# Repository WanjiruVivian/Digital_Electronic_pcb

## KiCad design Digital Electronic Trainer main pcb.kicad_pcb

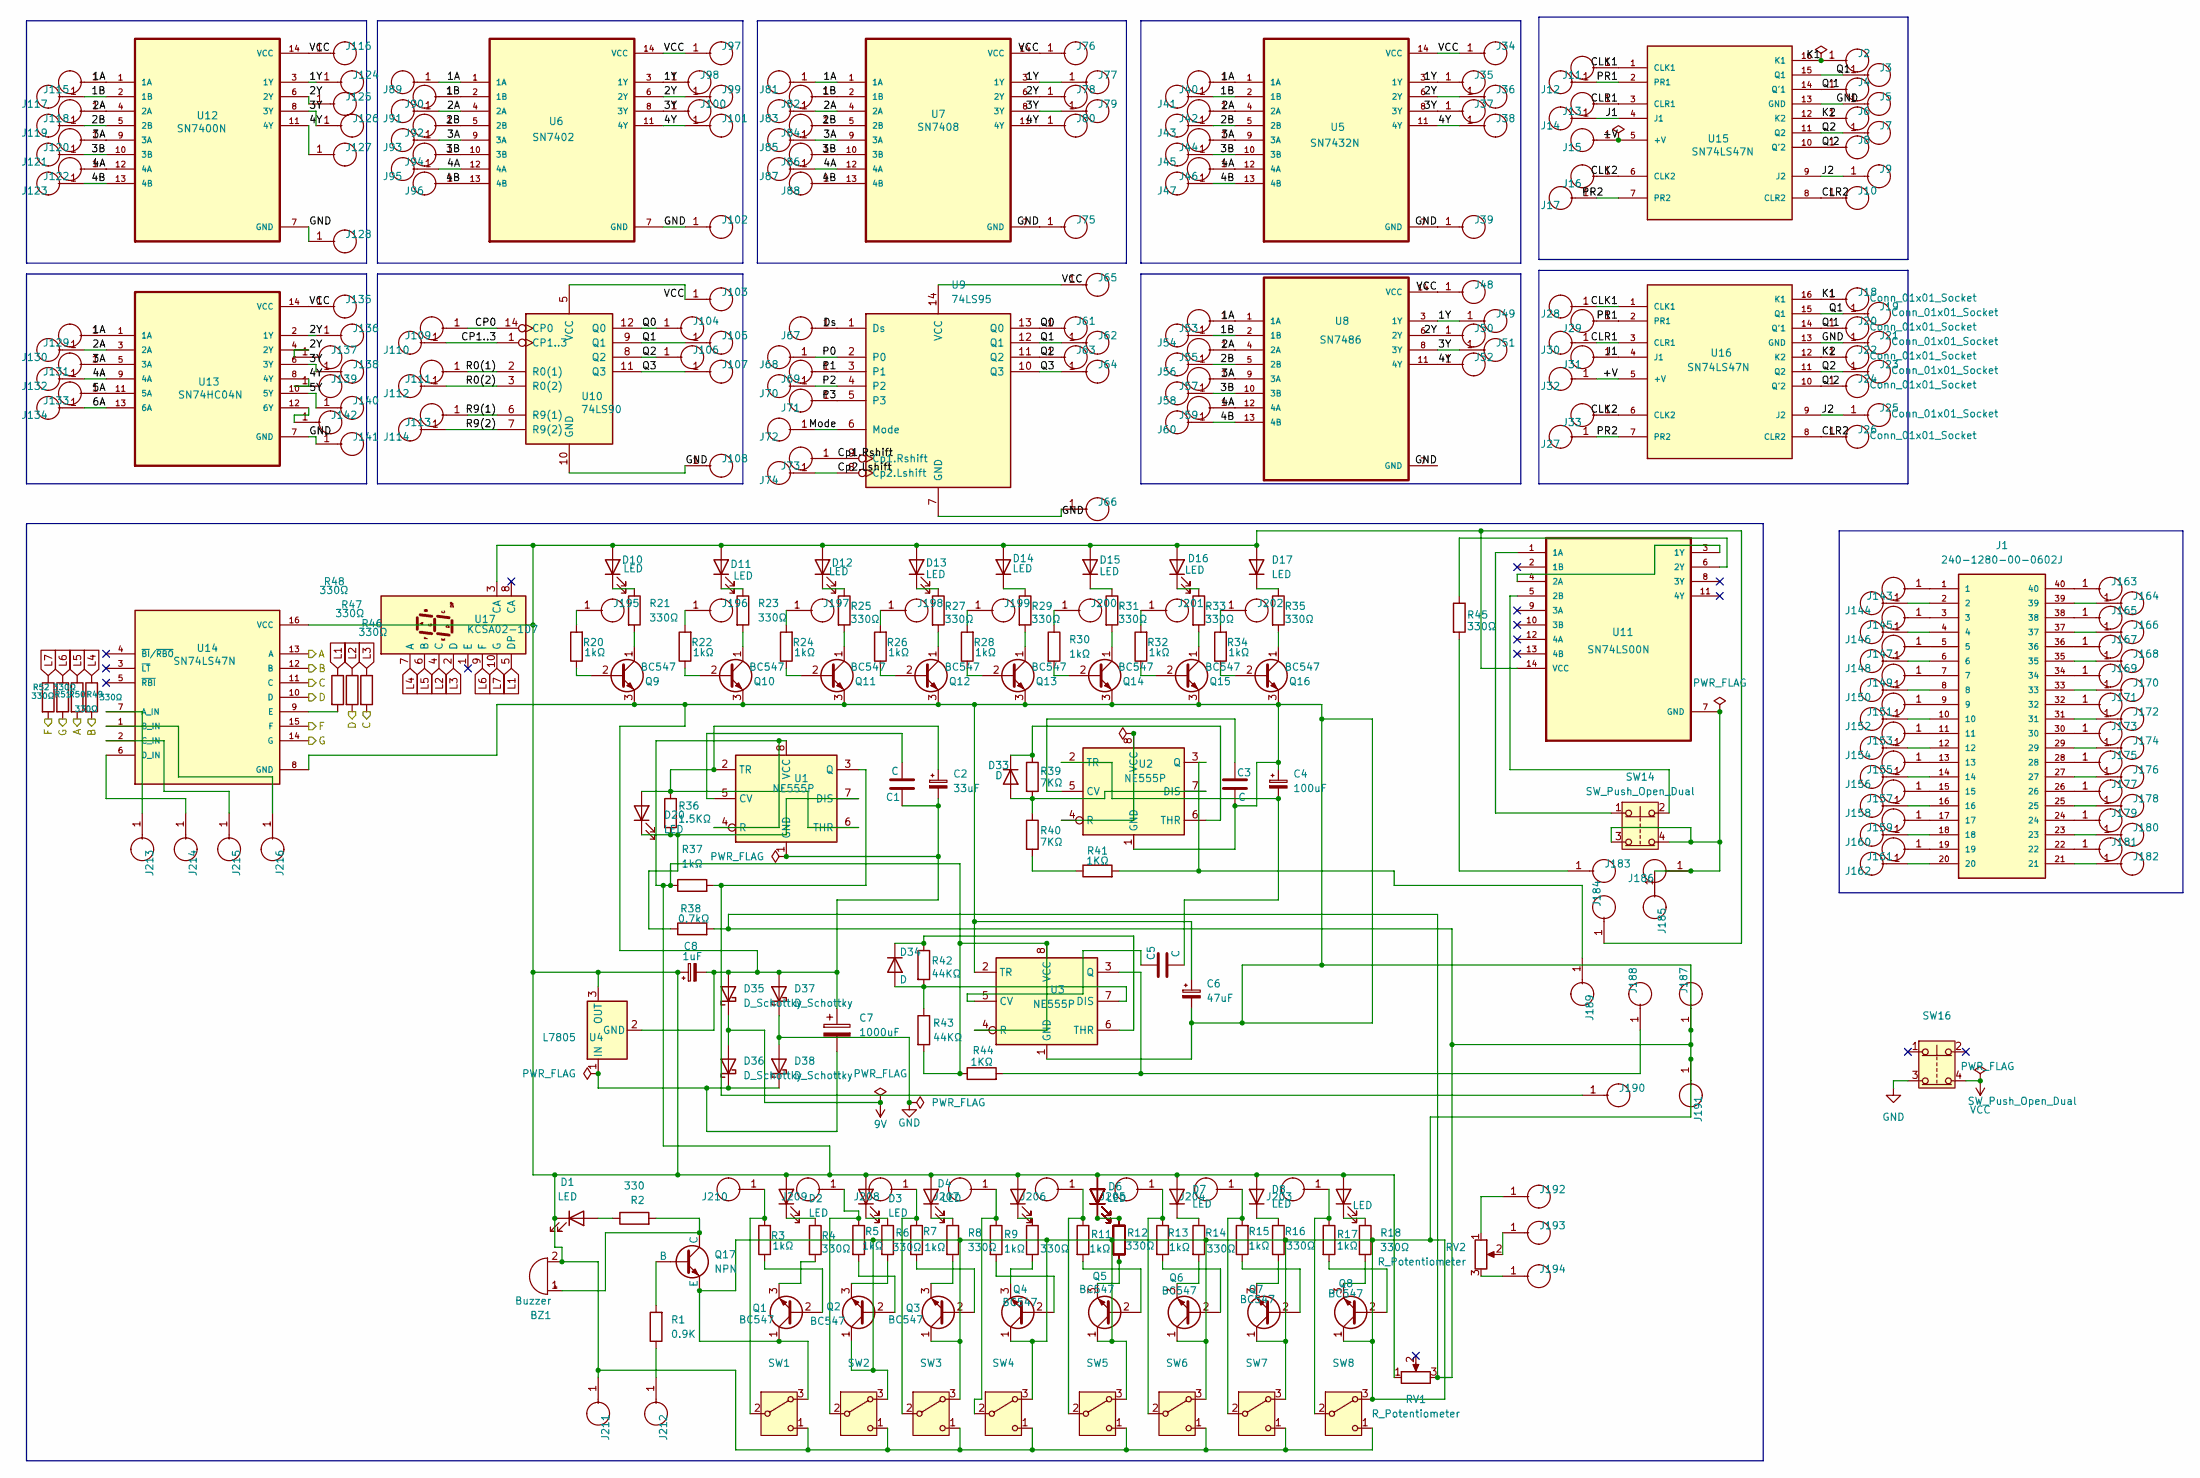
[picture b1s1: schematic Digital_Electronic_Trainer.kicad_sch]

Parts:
BZ1: Buzzer; Buzzer_D14mm_H7mm_P10mm
C1, C3, C5: C; C_Disc_D10.0mm_W2.5mm_P5.00mm
C2: 33uF; C_Radial_D10.0mm_H16.0mm_P5.00mm
C4: 100uF; C_Radial_D10.0mm_H16.0mm_P5.00mm
C6: 47uF; C_Radial_D10.0mm_H16.0mm_P5.00mm
C7: 1000uF; C_Radial_D12.5mm_H25.0mm_P5.00mm
C8: 1uF; C_Radial_D5.0mm_H11.0mm_P2.00mm
D1, D2, D3, D4, D5, D6, D7, D8, D9, D10, D11, D12, D13, D14, D15, D16, D17, D20, D24, D25, D26: LED; LED_D5.0mm
D33, D34: D; D_DO-34_SOD68_P12.70mm_Horizontal
D35, D36, D37, D38: D_Schottky; D_A-405_P12.70mm_Horizontal
J1: 240-1280-00-0602J; 3M_240-1280-00-0602J; PARTREV E
J2, J3, J4, J5, J6, J7, J8, J9, J10, J11, J12, J13, J14, J15, J16, J17, J18, J19, J20, J21, J22, J23, J24, J25, J26, J27, J28, J29, J30, J31, J32, J33, J34, J35, J36, J37, J38, J39, J40, J41, J42, J43, J44, J45, J46, J47, J48, J49, J50, J51, J52, J53, J54, J55, J56, J57, J58, J59, J60, J61, J62, J63, J64, J65, J66, J67, J68, J69, J70, J71, J72, J73, J74, J75, J76, J77, J78, J79, J80, J81, J82, J83, J84, J85, J86, J87, J88, J89, J90, J91, J92, J93, J94, J95, J96, J97, J98, J99, J100, J101, J102, J103, J104, J105, J106, J107, J108, J109, J110, J111, J112, J113, J114, J115, J116, J117, J118, J119, J120, J121, J122, J123, J124, J125, J126, J127, J128, J129, J130, J131, J132, J133, J134, J135, J136, J137, J138, J139, J140, J141, J142, J143, J144, J145, J146, J147, J148, J149, J150, J151, J152, J153, J154, J155, J156, J157, J158, J159, J160, J161, J162, J163, J164, J165, J166, J167, J168, J169, J170, J171, J172, J173, J174, J175, J176, J177, J178, J179, J180, J181, J182, J183, J184, J185, J186, J187, J188, J189, J190, J191, J192, J193, J194, J195, J196, J197, J198, J199, J200, J201, J202, J203, J204, J205, J206, J207, J208, J209, J210, J211, J212, J213, J214, J215, J216: Conn_01x01_Socket; PinSocket_1x01_P2.00mm_Vertical
Q1, Q2, Q3, Q4, Q5, Q6, Q7, Q8, Q9, Q10, Q11, Q12, Q13, Q14, Q15, Q16: BC547; TO-92_Inline
Q17: NPN; TO18
R1: 0.9K; R_Axial_DIN0309_L9.0mm_D3.2mm_P15.24mm_Horizontal
R2: 330; R_Axial_DIN0309_L9.0mm_D3.2mm_P15.24mm_Horizontal
R3, R5, R7, R9, R11, R13, R15, R17, R20, R22, R24, R26, R28, R30, R32, R34, R37: 1kΩ; R_Axial_DIN0309_L9.0mm_D3.2mm_P15.24mm_Horizontal
R4, R6, R8, R10, R12, R14, R16, R18, R21, R23, R25, R27, R29, R31, R33, R35: 330Ω; R_Axial_DIN0309_L9.0mm_D3.2mm_P15.24mm_Horizontal
R36: 1.5KΩ; R_Axial_DIN0309_L9.0mm_D3.2mm_P15.24mm_Horizontal
R38: 0.7kΩ; R_Axial_DIN0309_L9.0mm_D3.2mm_P15.24mm_Horizontal
R39, R40: 7KΩ; R_Axial_DIN0309_L9.0mm_D3.2mm_P15.24mm_Horizontal
R41, R44: 1KΩ; R_Axial_DIN0309_L9.0mm_D3.2mm_P15.24mm_Horizontal
R42, R43: 44KΩ; R_Axial_DIN0309_L9.0mm_D3.2mm_P15.24mm_Horizontal
R45, R46, R47, R48, R49, R50, R51, R52, R53, R55, R56: 330Ω; R_Axial_DIN0207_L6.3mm_D2.5mm_P15.24mm_Horizontal
RV1, RV2: R_Potentiometer; Potentiometer_Alps_RK09K_Single_Vertical
SW1, SW2, SW3, SW4, SW5, SW6, SW7, SW8: SW_Nidec_CAS-120A1; SW_ATE1D-2M3-10-Z
SW14: SW_Push_Open_Dual; SW_Push_2P1T_Toggle_CK_PVA1xxH2xxxxxxV2
SW16: SW_Push_Open_Dual; Push_E-Switch_KS01Q01
U1, U2, U3: NE555P; DIP-8_W7.62mm
U4: L7805; TO255P1040X460X1968-3
U5: SN7432N; DIP794W45P254L1969H508Q14
U6: SN7402; DIP794W45P254L1969H508Q14
U7: SN7408; DIP794W45P254L1969H508Q14
U8: SN7486; DIP794W45P254L1969H508Q14
U9: 74LS95; DIP794W45P254L1969H508Q16
U10: 74LS90; DIP254P762X508-14
U11: SN74LS00N; DIP794W45P254L1969H508Q14; DigiKey_Part_Number 296-1626-ND
U12: SN7400N; DIP794W45P254L1969H508Q14
U13: SN74HC04N; DIP794W45P254L1969H508Q14; DigiKey_Part_Number 2156-SN74HC04N-ND
U14: SN74LS47N; DIP794W45P254L1930H508Q16; PARTREV 12/2002; DigiKey_Part_Number 2156-SN74LS47N-ND
U15, U16: SN74LS47N; DIP794W45P254L1930H508Q16
U17: KCSA02-107; KCSC02-107

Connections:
9V: D35.1 (K), D36.2 (A)
/1A: J40.1, J53.1, J81.1, J89.1, J115.1, J129.1, U5.1 (1A), U6.1 (1A), U7.1 (1A), U8.1 (1A), U12.1 (1A), U13.1 (1A); also elsewhere on the board
/1B: J41.1, J54.1, J82.1, J90.1, J117.1, U5.2 (1B), U6.2 (1B), U7.2 (1B), U8.2 (1B), U12.2 (1B); also elsewhere on the board
/2A: J42.1, J55.1, J83.1, J91.1, J118.1, J130.1, U5.4 (2A), U6.4 (2A), U7.4 (2A), U8.4 (2A), U12.4 (2A), U13.3 (2A); also elsewhere on the board
/2B: J43.1, J56.1, J84.1, J92.1, J119.1, U5.5 (2B), U6.5 (2B), U7.5 (2B), U8.5 (2B), U12.5 (2B); also elsewhere on the board
/3A: J44.1, J57.1, J85.1, J93.1, J120.1, J131.1, U5.9 (3A), U6.9 (3A), U7.9 (3A), U8.9 (3A), U12.9 (3A), U13.5 (3A); also elsewhere on the board
/3B: J45.1, J58.1, J86.1, J94.1, J121.1, U5.10 (3B), U6.10 (3B), U7.10 (3B), U8.10 (3B), U12.10 (3B); also elsewhere on the board
/3Y: J37.1, J51.1, J79.1, J100.1, J126.1, J138.1, U5.8 (3Y), U6.8 (3Y), U7.8 (3Y), U8.8 (3Y), U12.8 (3Y), U13.6 (3Y); also elsewhere on the board
/4A: J46.1, J59.1, J87.1, J95.1, J122.1, J132.1, U5.12 (4A), U6.12 (4A), U7.12 (4A), U8.12 (4A), U12.12 (4A), U13.9 (4A); also elsewhere on the board
/4B: J47.1, J60.1, J88.1, J96.1, J123.1, U5.13 (4B), U6.13 (4B), U7.13 (4B), U8.13 (4B), U12.13 (4B); also elsewhere on the board
/4Y: J38.1, J52.1, J80.1, J101.1, J127.1, J139.1, U5.11 (4Y), U6.11 (4Y), U7.11 (4Y), U8.11 (4Y), U12.11 (4Y), U13.8 (4Y); also elsewhere on the board
/5A: J133.1, U13.11 (5A); also elsewhere on the board
/5Y: J140.1, U13.10 (5Y); also elsewhere on the board
/6A: J134.1, U13.13 (6A); also elsewhere on the board
/+V: J15.1, J32.1, U15.5 (+V), U16.5 (+V); also elsewhere on the board
/A: R50.2, U14.13 (A)
/B: R49.2, U14.12 (B)
/C: R46.2, U14.11 (C)
/CLK1: J11.1, J28.1, U15.1 (CLK1), U16.1 (CLK1); also elsewhere on the board
/CLK2: J16.1, J33.1, U15.6 (CLK2), U16.6 (CLK2); also elsewhere on the board
/CLR1: J13.1, J30.1, U15.3 (CLR1), U16.3 (CLR1); also elsewhere on the board
/CLR2: J10.1, J26.1, U15.8 (CLR2), U16.8 (CLR2); also elsewhere on the board
/CP0: J109.1, U10.14 (CP0); also elsewhere on the board
/CP1..3: J110.1, U10.1 (CP1..3); also elsewhere on the board
/Cp1.Rshift: J73.1, U9.9 (Cp1.Rshift); also elsewhere on the board
/Cp2.Lshift: J74.1, U9.8 (Cp2.Lshift); also elsewhere on the board
/D: R47.2, U14.10 (D)
/Ds: J67.1, U9.1 (Ds); also elsewhere on the board
/F: R52.2, U14.15 (F)
/G: R51.2, U14.14 (G)
/J1: J14.1, J31.1, U15.4 (J1), U16.4 (J1); also elsewhere on the board
/J2: J9.1, J25.1, U15.9 (J2), U16.9 (J2); also elsewhere on the board
/K1: J2.1, J18.1, U15.16 (K1), U16.16 (K1); also elsewhere on the board
/K2: J6.1, J22.1, U15.12 (K2), U16.12 (K2); also elsewhere on the board
/Mode: J72.1, U9.6 (Mode); also elsewhere on the board
/P0: J68.1, U9.2 (P0); also elsewhere on the board
/P1: J69.1, U9.3 (P1); also elsewhere on the board
/P2: J70.1, U9.4 (P2); also elsewhere on the board
/P3: J71.1, U9.5 (P3); also elsewhere on the board
/PR1: J12.1, J29.1, U15.2 (PR1), U16.2 (PR1); also elsewhere on the board
/PR2: J17.1, J27.1, U15.7 (PR2), U16.7 (PR2); also elsewhere on the board
/Q0: J61.1, J104.1, U9.13 (Q0), U10.12 (Q0); also elsewhere on the board
/Q2: J7.1, J23.1, J63.1, J106.1, U9.11 (Q2), U10.8 (Q2), U15.11 (Q2), U16.11 (Q2); also elsewhere on the board
/Q3: J64.1, J107.1, U9.10 (Q3), U10.11 (Q3); also elsewhere on the board
/Q'2: J8.1, J24.1, U15.10 (Q'2), U16.10 (Q'2); also elsewhere on the board
/R0(1): J111.1, U10.2 (R0(1)); also elsewhere on the board
/R0(2): J112.1, U10.3 (R0(2)); also elsewhere on the board
/R9(1): J113.1, U10.6 (R9(1)); also elsewhere on the board
/R9(2): J114.1, U10.7 (R9(2)); also elsewhere on the board
L1: R48.1, U17.5 (DP)
L2: R47.1, U17.4 (C)
L3: R46.1, U17.2 (D)
L4: R49.1, U17.7 (A)
L5: R50.1, U17.6 (B)
L6: R51.1, U17.9 (F)
L7: R52.1, U17.10 (G)
unnamed: BZ1.1 (+), Q17.1 (C), R2.2
unnamed: BZ1.2 (-), C8.1, D1.1 (K), D2.2 (A), D3.2 (A), D4.2 (A), D5.2 (A), D6.2 (A), D7.2 (A), D8.2 (A), D9.2 (A), D10.2 (A), D11.2 (A), D12.2 (A), D13.2 (A), D14.2 (A), D15.2 (A), D16.2 (A), D17.2 (A), D24.2 (A), D25.2 (A), D26.2 (A), J184.1, J211.1, R37.1, R43.2, R44.1, RV1.1, SW1.1 (C), SW2.1 (C), SW3.1 (C), SW4.1 (C), SW5.1 (C), SW6.1 (C), SW7.1 (C), SW8.1 (C), U1.4 (R), U1.8 (VCC), U3.4 (R), U3.8 (VCC), U4.3 (OUT), U11.14 (VCC), U14.16 (VCC), U17.3 (CA)
unnamed: D1.2 (A), R2.1
unnamed: D2.1 (K), R4.1
unnamed: D3.1 (K), R6.1
unnamed: D4.1 (K), R8.1
unnamed: D5.1 (K), R10.1
unnamed: D6.1 (K), D24.1 (K), D25.1 (K), D26.1 (K), R12.1, R53.1, R55.1, R56.1
unnamed: D7.1 (K), R14.1
unnamed: D8.1 (K), R16.1
unnamed: D9.1 (K), R18.1
unnamed: D10.1 (K), R21.1
unnamed: D11.1 (K), R23.1
unnamed: D12.1 (K), R25.1
unnamed: D13.1 (K), R27.1
unnamed: D14.1 (K), R29.1
unnamed: D15.1 (K), R31.1
unnamed: D16.1 (K), R33.1
unnamed: D17.1 (K), R35.1
unnamed: C2.1, D20.2 (A), R36.1, U1.2 (TR), U1.6 (THR)
unnamed: D20.1 (K), R36.2, R38.1, U1.7 (DIS)
unnamed: D33.2 (A), R39.2, R40.1, U2.7 (DIS)
unnamed: D33.1 (K), R39.1, U2.6 (THR)
unnamed: D34.2 (A), R42.2, R43.1, U3.7 (DIS)
unnamed: D34.1 (K), R42.1, U3.6 (THR)
unnamed: C1.1, C2.2, C3.2, C4.1, C6.1, C6.2, C7.1, C8.2, D35.2 (A), D37.2 (A), J187.1, J191.1, Q1.1 (C), Q2.1 (C), Q3.1 (C), Q4.1 (C), Q5.1 (C), Q6.1 (C), Q7.1 (C), Q8.1 (C), Q9.3 (E), Q10.3 (E), Q11.3 (E), Q12.3 (E), Q13.3 (E), Q14.3 (E), Q15.3 (E), Q16.3 (E), Q17.3 (E), R38.2, RV1.3, SW1.3 (A), SW2.3 (A), SW3.3 (A), SW4.3 (A), SW5.3 (A), SW6.3 (A), SW7.3 (A), SW8.3 (A), U1.1 (GND), U2.1 (GND), U3.1 (GND), U3.2 (TR), U4.2 (GND), U14.8 (GND)
unnamed: C7.2, D36.1 (K), D38.1 (K), U4.1 (IN)
unnamed 83: J142.1, U13.12 (6Y); also elsewhere on the board
unnamed: J1.1, J143.1
unnamed: J1.2, J144.1
unnamed: J1.3, J145.1
unnamed: J1.4, J146.1
unnamed: J1.5, J147.1
unnamed: J1.6, J148.1
unnamed: J1.7, J149.1
unnamed: J1.8, J150.1
unnamed: J1.9, J151.1
unnamed: J1.10, J152.1
unnamed: J1.11, J153.1
unnamed: J1.12, J154.1
unnamed: J1.13, J155.1
unnamed: J1.14, J156.1
unnamed: J1.15, J157.1
unnamed: J1.16, J158.1
unnamed: J1.17, J159.1
unnamed: J1.18, J160.1
unnamed: J1.19, J161.1
unnamed: J1.20, J162.1
unnamed: J1.40, J163.1
unnamed: J1.39, J164.1
unnamed: J1.38, J165.1
unnamed: J1.37, J166.1
unnamed: J1.36, J167.1
unnamed: J1.35, J168.1
unnamed: J1.34, J169.1
unnamed: J1.33, J170.1
unnamed: J1.32, J171.1
unnamed: J1.31, J172.1
unnamed: J1.30, J173.1
unnamed: J1.29, J174.1
unnamed: J1.28, J175.1
unnamed: J1.27, J176.1
unnamed: J1.26, J177.1
unnamed: J1.25, J178.1
unnamed: J1.24, J179.1
unnamed: J1.23, J180.1
unnamed: J1.22, J181.1
unnamed: J1.21, J182.1
unnamed: J183.1, R45.2
unnamed: J185.1, J186.1, SW14.3, SW14.4, U11.7 (GND)
unnamed: J188.1, R44.2, U3.3 (Q)
unnamed: J189.1, R41.2, U2.3 (Q)
unnamed: J190.1, R37.2, U1.3 (Q)
unnamed: J192.1, RV2.1
unnamed: J193.1, RV2.2
unnamed: J194.1, RV2.3
unnamed: J195.1, R20.2
unnamed: J196.1, R22.2
unnamed: J197.1, R24.2
unnamed: J198.1, R26.2
unnamed: J199.1, R28.2
unnamed: J200.1, R30.1
unnamed: J201.1, R32.2
unnamed: J202.1, R34.2
unnamed: J203.1, R17.1, SW8.2 (B)
unnamed: J204.1, R15.2, SW7.2 (B)
unnamed: J205.1, R13.1, SW6.2 (B)
unnamed: J206.1, R11.1, SW5.2 (B)
unnamed: J207.1, R9.1, SW4.2 (B)
unnamed: J208.1, R7.1, SW3.2 (B)
unnamed: J209.1, R5.1, SW2.2 (B)
unnamed: J210.1, R3.2, SW1.2 (B)
unnamed: J212.1, R1.1
unnamed: J213.1, U14.7 (A_IN)
unnamed: J214.1, U14.6 (D_IN)
unnamed: J215.1, U14.2 (C_IN)
unnamed: J216.1, U14.1 (B_IN)
unnamed: Q1.2 (B), R3.1
unnamed: Q1.3 (E), R4.2
unnamed: Q2.2 (B), R5.2
unnamed: Q2.3 (E), R6.2
unnamed: Q3.2 (B), R7.2
unnamed: Q3.3 (E), R8.2
unnamed: Q4.2 (B), R9.2
unnamed: Q4.3 (E), R10.2
unnamed: Q5.2 (B), R11.2
unnamed: Q5.3 (E), R12.2, R53.2, R55.2, R56.2
unnamed: Q6.2 (B), R13.2
unnamed: Q6.3 (E), R14.2
unnamed: Q7.2 (B), R15.1
unnamed: Q7.3 (E), R16.2
unnamed: Q8.2 (B), R17.2
unnamed: Q8.3 (E), R18.2
unnamed: Q9.2 (B), R20.1
unnamed: Q9.1 (C), R21.2
unnamed: Q10.2 (B), R22.1
unnamed: Q10.1 (C), R23.2
unnamed: Q11.2 (B), R24.1
unnamed: Q11.1 (C), R25.2
unnamed: Q12.2 (B), R26.1
unnamed: Q12.1 (C), R27.2
unnamed: Q13.2 (B), R28.1
unnamed: Q13.1 (C), R29.2
unnamed: Q14.2 (B), R30.2
unnamed: Q14.1 (C), R31.2
unnamed: Q15.2 (B), R32.1
unnamed: Q15.1 (C), R33.2
unnamed: Q16.2 (B), R34.1
unnamed: Q16.1 (C), R35.2
unnamed: Q17.2 (B), R1.2
unnamed: R40.2, R41.1
unnamed: C1.2, U1.5 (CV)
unnamed: C3.1, U2.5 (CV)
unnamed: U2.4 (R), U2.8 (VCC)
unnamed: C4.2, C5.2, U2.2 (TR)
unnamed: C5.1, U3.5 (CV)
unnamed: SW14.1, U11.1 (1A)
unnamed: U11.3 (1Y), U11.4 (2A)
unnamed: SW14.2, U11.5 (2B)
unnamed: R45.1, U11.6 (2Y)
unnamed: R48.2, U14.9 (E)
VCC: J34.1, J48.1, J65.1, J76.1, J97.1, J103.1, J116.1, J135.1, SW16.4, U5.14 (VCC), U6.14 (VCC), U7.14 (VCC), U8.14 (VCC), U9.14 (VCC), U10.5 (VCC), U12.14 (VCC), U13.14 (VCC); also elsewhere on the board

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
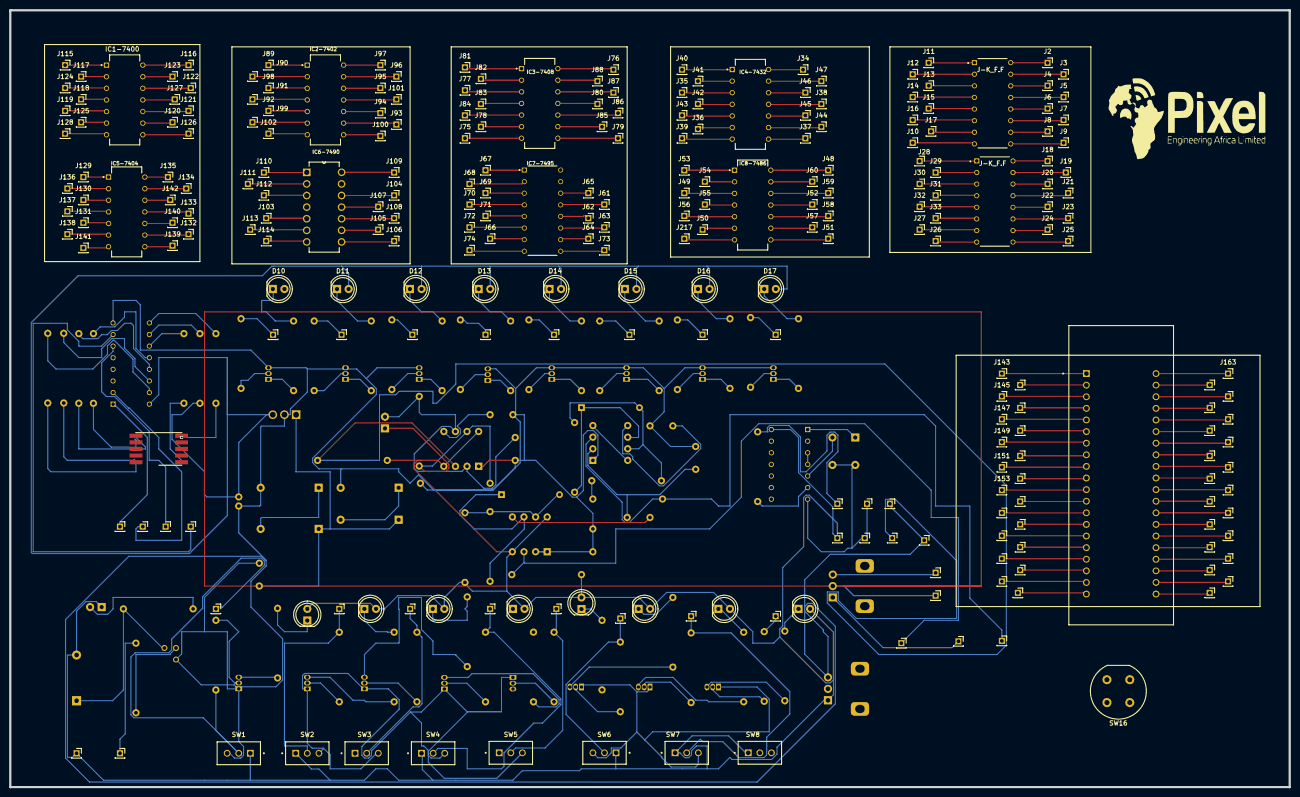
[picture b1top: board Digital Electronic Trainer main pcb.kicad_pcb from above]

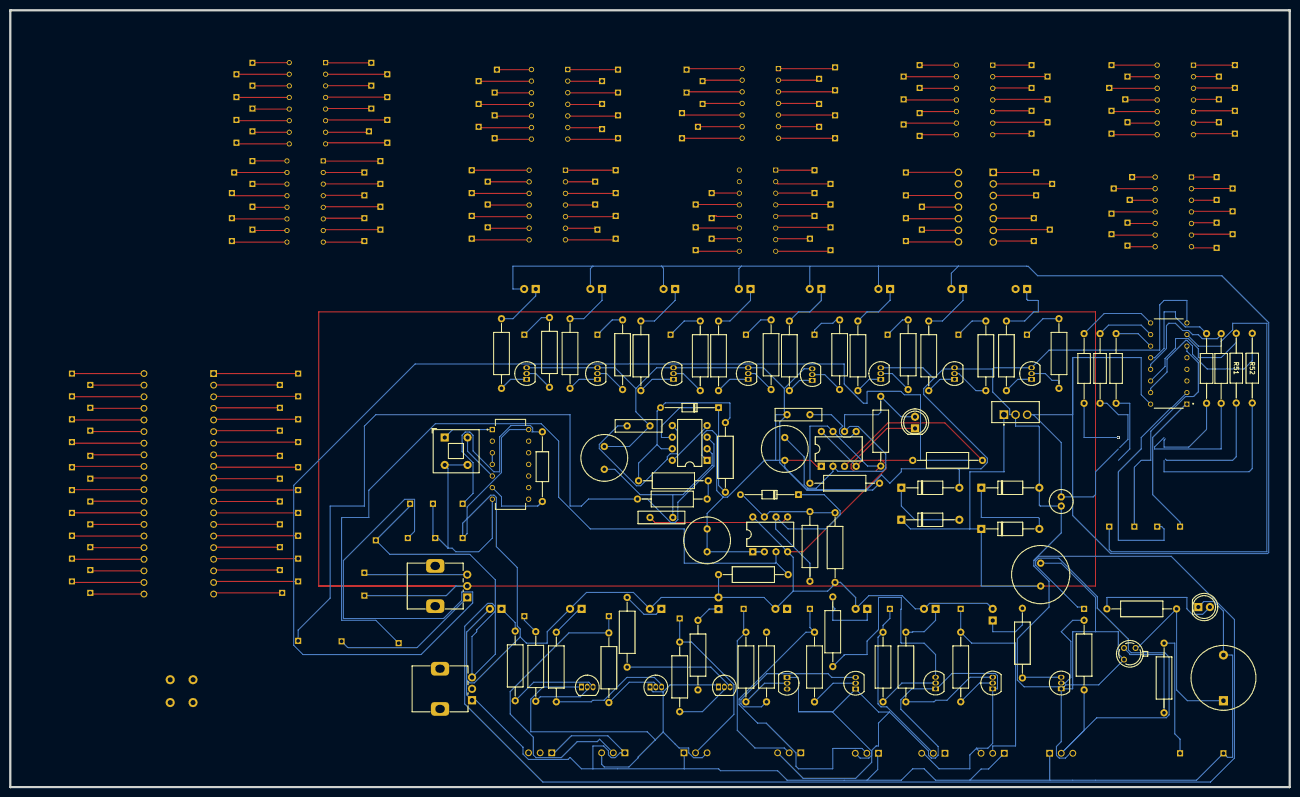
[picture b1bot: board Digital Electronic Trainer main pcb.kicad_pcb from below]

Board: 2 copper layers, 280.0 x 170.0 mm, 347 parts (94 on the bottom side), 208 nets.

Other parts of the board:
IC1-7400: SN7400N; DIP794W45P254L1969H508Q14
IC2-7402: SN7402; DIP794W45P254L1969H508Q14
IC3-7408: SN7408; DIP794W45P254L1969H508Q14
IC4-7432: SN7432N; DIP794W45P254L1969H508Q14
IC5-7404: SN74HC04N; DIP794W45P254L1969H508Q14
IC6-7490: 74LS90; DIP254P762X508-14
IC7-7495: 74LS95; DIP794W45P254L1969H508Q16
IC8-7486: SN7486; DIP794W45P254L1969H508Q14
J217: Conn_01x01_Socket; PinSocket_1x01_P2.00mm_Vertical
J-K_F.F, J-K_F.F#2: J-K F.F; DIP794W45P254L1930H508Q16

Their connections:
/1A: IC1-7400.1 (1A), IC2-7402.1 (1A), IC3-7408.1 (1A), IC4-7432.1 (1A), IC5-7404.1 (1A), IC8-7486.1 (1A); also elsewhere on the board
/1B: IC1-7400.2 (1B), IC2-7402.2 (1B), IC3-7408.2 (1B), IC4-7432.2 (1B), IC8-7486.2 (1B); also elsewhere on the board
/2A: IC1-7400.4 (2A), IC2-7402.4 (2A), IC3-7408.4 (2A), IC4-7432.4 (2A), IC5-7404.3 (2A), IC8-7486.4 (2A); also elsewhere on the board
/2B: IC1-7400.5 (2B), IC2-7402.5 (2B), IC3-7408.5 (2B), IC4-7432.5 (2B), IC8-7486.5 (2B); also elsewhere on the board
/3A: IC1-7400.9 (3A), IC2-7402.9 (3A), IC3-7408.9 (3A), IC4-7432.9 (3A), IC5-7404.5 (3A), IC8-7486.9 (3A); also elsewhere on the board
/3B: IC1-7400.10 (3B), IC2-7402.10 (3B), IC3-7408.10 (3B), IC4-7432.10 (3B), IC8-7486.10 (3B); also elsewhere on the board
/3Y: IC1-7400.8 (3Y), IC2-7402.8 (3Y), IC3-7408.8 (3Y), IC4-7432.8 (3Y), IC5-7404.6 (3Y), IC8-7486.8 (3Y); also elsewhere on the board
/4A: IC1-7400.12 (4A), IC2-7402.12 (4A), IC3-7408.12 (4A), IC4-7432.12 (4A), IC5-7404.9 (4A), IC8-7486.12 (4A); also elsewhere on the board
/4B: IC1-7400.13 (4B), IC2-7402.13 (4B), IC3-7408.13 (4B), IC4-7432.13 (4B), IC8-7486.13 (4B); also elsewhere on the board
/4Y: IC1-7400.11 (4Y), IC2-7402.11 (4Y), IC3-7408.11 (4Y), IC4-7432.11 (4Y), IC5-7404.8 (4Y), IC8-7486.11 (4Y); also elsewhere on the board
/5A: IC5-7404.11 (5A); also elsewhere on the board
/5Y: IC5-7404.10 (5Y); also elsewhere on the board
/6A: IC5-7404.13 (6A); also elsewhere on the board
/+V: J-K_F.F.5 (+V), J-K_F.F#2.5 (+V); also elsewhere on the board
/CLK1: J-K_F.F.1 (CLK1), J-K_F.F#2.1 (CLK1); also elsewhere on the board
/CLK2: J-K_F.F.6 (CLK2), J-K_F.F#2.6 (CLK2); also elsewhere on the board
/CLR1: J-K_F.F.3 (CLR1), J-K_F.F#2.3 (CLR1); also elsewhere on the board
/CLR2: J-K_F.F.8 (CLR2), J-K_F.F#2.8 (CLR2); also elsewhere on the board
/CP0: IC6-7490.14 (CP0); also elsewhere on the board
/CP1..3: IC6-7490.1 (CP1..3); also elsewhere on the board
/Cp1.Rshift: IC7-7495.9 (Cp1.Rshift); also elsewhere on the board
/Cp2.Lshift: IC7-7495.8 (Cp2.Lshift); also elsewhere on the board
/Ds: IC7-7495.1 (Ds); also elsewhere on the board
/J1: J-K_F.F.4 (J1), J-K_F.F#2.4 (J1); also elsewhere on the board
/J2: J-K_F.F.9 (J2), J-K_F.F#2.9 (J2); also elsewhere on the board
/K1: J-K_F.F.16 (K1), J-K_F.F#2.16 (K1); also elsewhere on the board
/K2: J-K_F.F.12 (K2), J-K_F.F#2.12 (K2); also elsewhere on the board
/Mode: IC7-7495.6 (Mode); also elsewhere on the board
/P0: IC7-7495.2 (P0); also elsewhere on the board
/P1: IC7-7495.3 (P1); also elsewhere on the board
/P2: IC7-7495.4 (P2); also elsewhere on the board
/P3: IC7-7495.5 (P3); also elsewhere on the board
/PR1: J-K_F.F.2 (PR1), J-K_F.F#2.2 (PR1); also elsewhere on the board
/PR2: J-K_F.F.7 (PR2), J-K_F.F#2.7 (PR2); also elsewhere on the board
/Q0: IC6-7490.12 (Q0), IC7-7495.13 (Q0); also elsewhere on the board
/Q2: IC6-7490.8 (Q2), IC7-7495.11 (Q2), J-K_F.F.11 (Q2), J-K_F.F#2.11 (Q2); also elsewhere on the board
/Q3: IC6-7490.11 (Q3), IC7-7495.10 (Q3); also elsewhere on the board
/Q'2: J-K_F.F.10 (Q'2), J-K_F.F#2.10 (Q'2); also elsewhere on the board
/R0(1): IC6-7490.2 (R0(1)); also elsewhere on the board
/R0(2): IC6-7490.3 (R0(2)); also elsewhere on the board
/R9(1): IC6-7490.6 (R9(1)); also elsewhere on the board
/R9(2): IC6-7490.7 (R9(2)); also elsewhere on the board
unnamed 83: IC5-7404.12 (6Y); also elsewhere on the board
VCC: IC1-7400.14 (VCC), IC2-7402.14 (VCC), IC3-7408.14 (VCC), IC4-7432.14 (VCC), IC5-7404.14 (VCC), IC6-7490.5 (VCC), IC7-7495.14 (VCC), IC8-7486.14 (VCC); also elsewhere on the board

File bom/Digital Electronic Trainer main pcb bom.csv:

"Id";"Designator";"Footprint";"Quantity";"Designation";"Supplier and ref";
1;"J215,J118,J166,J183,J128,J165,J150,J203,J74,J76,J86,J151,J106,J137,J188,J139,J104,J194,J157,J68,J120,J41,J117,J178,J52,J58,J177,J211,J24,J16,J17,J197,J204,J134,J143,J217,J34,J56,J29,J23,J132,J172,J107,J96,J189,J8,J196,J57,J40,J36,J99,J205,J59,J3,J101,J142,J193,J67,J131,J18,J123,J7,J167,J64,J9,J116,J108,J61,J213,J39,J154,J115,J77,J124,J174,J91,J158,J54,J27,J22,J2,J21,J62,J92,J186,J19,J168,J156,J28,J133,J160,J45,J161,J114,J11,J69,J185,J50,J195,J182,J112,J25,J119,J60,J75,J109,J149,J83,J181,J73,J163,J93,J184,J48,J111,J136,J88,J147,J46,J199,J145,J15,J200,J79,J210,J144,J95,J155,J47,J176,J20,J125,J190,J5,J141,J130,J89,J87,J207,J100,J121,J201,J206,J33,J146,J51,J42,J63,J98,J105,J13,J97,J135,J110,J14,J122,J113,J169,J103,J216,J32,J159,J129,J209,J208,J38,J31,J71,J65,J44,J66,J53,J212,J10,J198,J70,J164,J12,J192,J72,J78,J30,J82,J127,J148,J152,J138,J214,J43,J191,J6,J4,J179,J55,J94,J35,J170,J37,J84,J171,J102,J180,J85,J80,J202,J187,J175,J153,J26,J140,J90,J126,J49,J81,J173,J162";"PinSocket_1x01_P2.00mm_Vertical";216;"Conn_01x01_Socket";;;
2;"SW4,SW7,SW1,SW8,SW2,SW3,SW6,SW5";"SW_ATE1D-2M3-10-Z";8;"SW_Nidec_CAS-120A1";;;
3;"D17,D6,D15,D10,D12,D13,D4,D8,D11,D5,D14,D3,D16,D2,D9,D7,D20,D1";"LED_D5.0mm";18;"LED";;;
4;"IC3-7408";"DIP794W45P254L1969H508Q14";1;"SN7408";;;
5;"U17";"KCSC02-107";1;"KCSA02-107";;;
6;"IC8-7486";"DIP794W45P254L1969H508Q14";1;"SN7486";;;
7;"SW16";"Push_E-Switch_KS01Q01";1;"SW_Push_Open_Dual";;;
8;"IC6-7490";"DIP254P762X508-14";1;"74LS90";;;
9;"J-K_F.F,J-K_F.F";"DIP794W45P254L1930H508Q16";2;"J-K F.F";;;
10;"J1";"3M_240-1280-00-0602J";1;"240-1280-00-0602J";;;
11;"IC2-7402";"DIP794W45P254L1969H508Q14";1;"SN7402";;;
12;"IC4-7432";"DIP794W45P254L1969H508Q14";1;"SN7432N";;;
13;"IC5-7404";"DIP794W45P254L1969H508Q14";1;"SN74HC04N";;;
14;"IC1-7400";"DIP794W45P254L1969H508Q14";1;"SN7400N";;;
15;"IC7-7495";"DIP794W45P254L1969H508Q16";1;"74LS95";;;
16;"R12,R8,R35,R14,R21,R16,R29,R23,R25,R27,R10,R31,R18,R4,R33,R6";"R_Axial_DIN0309_L9.0mm_D3.2mm_P15.24mm_Horizontal";16;"330Ω";;;
17;"Q12,Q1,Q2,Q10,Q16,Q14,Q3,Q4,Q11,Q7,Q13,Q15,Q5,Q8,Q6,Q9";"TO-92_Inline";16;"BC547";;;
18;"RV1,RV2";"Potentiometer_Alps_RK09K_Single_Vertical";2;"R_Potentiometer";;;
19;"R3,R22,R11,R32,R17,R7,R13,R26,R24,R15,R34,R20,R9,R37,R30,R28,R5";"R_Axial_DIN0309_L9.0mm_D3.2mm_P15.24mm_Horizontal";17;"1kΩ";;;
20;"D38,D37,D36,D35";"D_A-405_P12.70mm_Horizontal";4;"D_Schottky";;;
21;"Q17";"TO18";1;"NPN";;;
22;"U3,U1,U2";"DIP-8_W7.62mm";3;"NE555P";;;
23;"C2";"C_Radial_D10.0mm_H16.0mm_P5.00mm";1;"33uF";;;
24;"R40,R39";"R_Axial_DIN0309_L9.0mm_D3.2mm_P15.24mm_Horizontal";2;"7KΩ";;;
25;"C6";"C_Radial_D10.0mm_H16.0mm_P5.00mm";1;"47uF";;;
26;"R42,R43";"R_Axial_DIN0309_L9.0mm_D3.2mm_P15.24mm_Horizontal";2;"44KΩ";;;
27;"R47,R52,R51,R46,R50,R45,R49,R48";"R_Axial_DIN0207_L6.3mm_D2.5mm_P15.24mm_Horizontal";8;"330Ω";;;
28;"R36";"R_Axial_DIN0309_L9.0mm_D3.2mm_P15.24mm_Horizontal";1;"1.5KΩ";;;
29;"SW14";"SW_Push_2P1T_Toggle_CK_PVA1xxH2xxxxxxV2";1;"SW_Push_Open_Dual";;;
30;"R44,R41";"R_Axial_DIN0309_L9.0mm_D3.2mm_P15.24mm_Horizontal";2;"1KΩ";;;
31;"C8";"C_Radial_D5.0mm_H11.0mm_P2.00mm";1;"1uF";;;
32;"BZ1";"Buzzer_D14mm_H7mm_P10mm";1;"Buzzer";;;
33;"D34,D33";"D_DO-34_SOD68_P12.70mm_Horizontal";2;"D";;;
34;"C5,C1,C3";"C_Disc_D10.0mm_W2.5mm_P5.00mm";3;"C";;;
35;"U14";"DIP794W45P254L1930H508Q16";1;"SN74LS47N";;;
36;"U4";"TO255P1040X460X1968-3";1;"L7805";;;
37;"R2";"R_Axial_DIN0309_L9.0mm_D3.2mm_P15.24mm_Horizontal";1;"330";;;
38;"R1";"R_Axial_DIN0309_L9.0mm_D3.2mm_P15.24mm_Horizontal";1;"0.9K";;;
39;"C4";"C_Radial_D10.0mm_H16.0mm_P5.00mm";1;"100uF";;;
40;"R38";"R_Axial_DIN0309_L9.0mm_D3.2mm_P15.24mm_Horizontal";1;"0.7kΩ";;;
41;"C7";"C_Radial_D12.5mm_H25.0mm_P5.00mm";1;"1000uF";;;
42;"U11";"DIP794W45P254L1969H508Q14";1;"SN74LS00N";;;

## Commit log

2024-11-21 Printed circuit design for digital electronic lab trainer files
